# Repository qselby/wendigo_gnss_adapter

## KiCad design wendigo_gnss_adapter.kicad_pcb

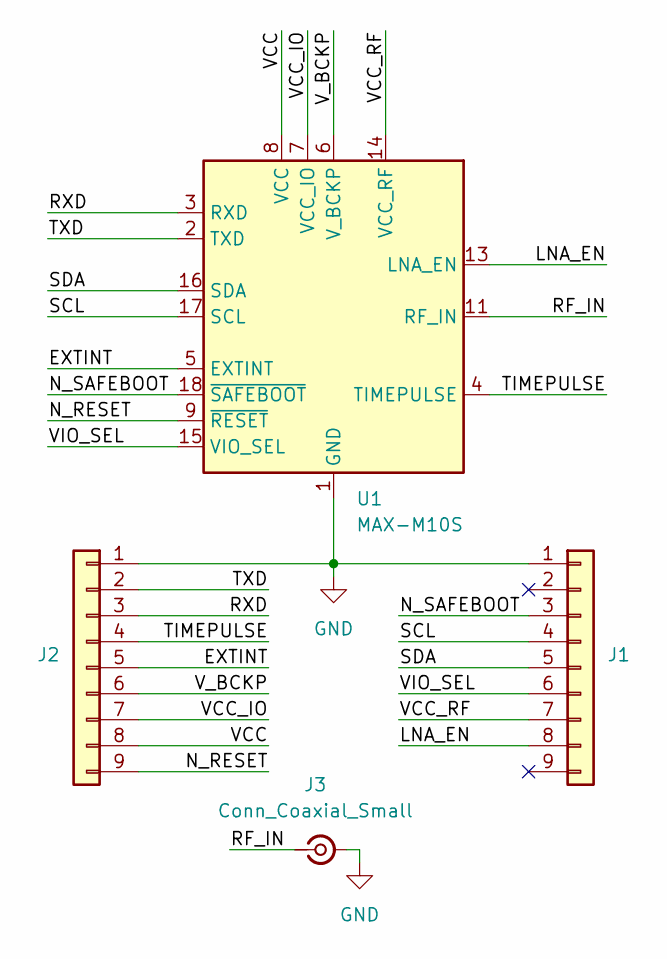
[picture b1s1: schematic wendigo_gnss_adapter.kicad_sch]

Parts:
J1, J2: Conn_01x09; PinHeader_1x09_P2.54mm_Vertical
J3: Conn_Coaxial_Small; U.FL_Molex_MCRF_73412-0110_Vertical
U1: MAX-M10S; ublox_MAX

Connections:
/EXTINT: J2.5, U1.5 (EXTINT)
/LNA_EN: J1.8, U1.13 (LNA_EN)
/N_RESET: J2.9, U1.9 (~RESET)
/N_SAFEBOOT: J1.3, U1.18 (~SAFEBOOT)
/RF_IN: J3.1 (In), U1.11 (RF_IN)
/RXD: J2.3, U1.3 (RXD)
/SCL: J1.4, U1.17 (SCL)
/SDA: J1.5, U1.16 (SDA)
/TIMEPULSE: J2.4, U1.4 (TIMEPULSE)
/TXD: J2.2, U1.2 (TXD)
/VCC: J2.8, U1.8 (VCC)
/VCC_IO: J2.7, U1.7 (VCC_IO)
/VCC_RF: J1.7, U1.14 (VCC_RF)
/VIO_SEL: J1.6, U1.15 (VIO_SEL)
/V_BCKP: J2.6, U1.6 (V_BCKP)
GND: J1.1, J2.1, J3.2 (Ext), U1.1 (GND), U1.10 (GND), U1.12 (GND)

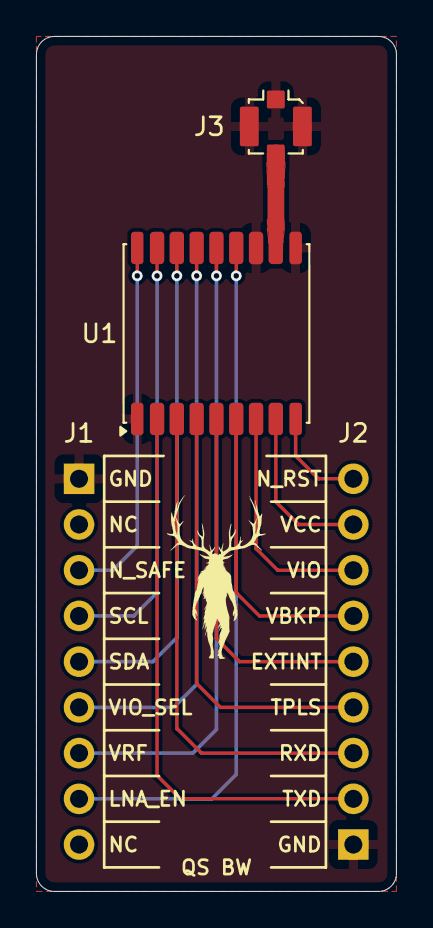
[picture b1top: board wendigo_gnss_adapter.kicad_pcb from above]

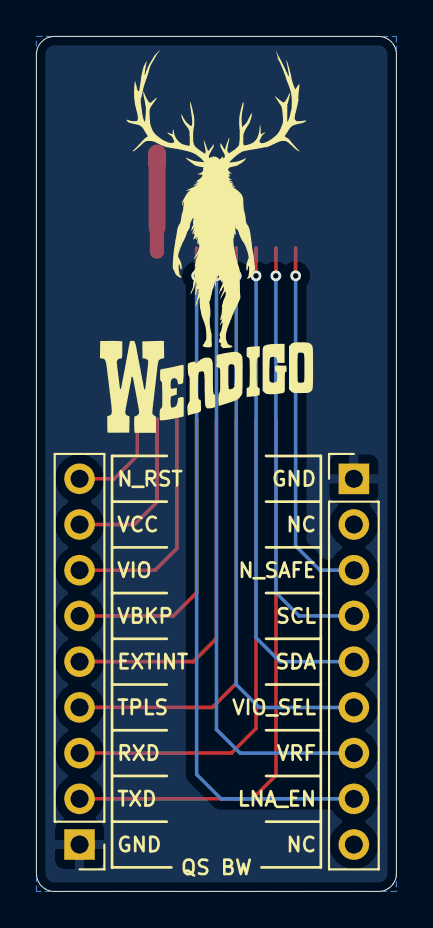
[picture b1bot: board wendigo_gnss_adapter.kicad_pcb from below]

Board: 2 copper layers, 20.0 x 47.5 mm, 4 parts (2 on the bottom side), 16 nets.

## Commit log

2026-05-05 First commit of the wendigo GNSS adapter.
